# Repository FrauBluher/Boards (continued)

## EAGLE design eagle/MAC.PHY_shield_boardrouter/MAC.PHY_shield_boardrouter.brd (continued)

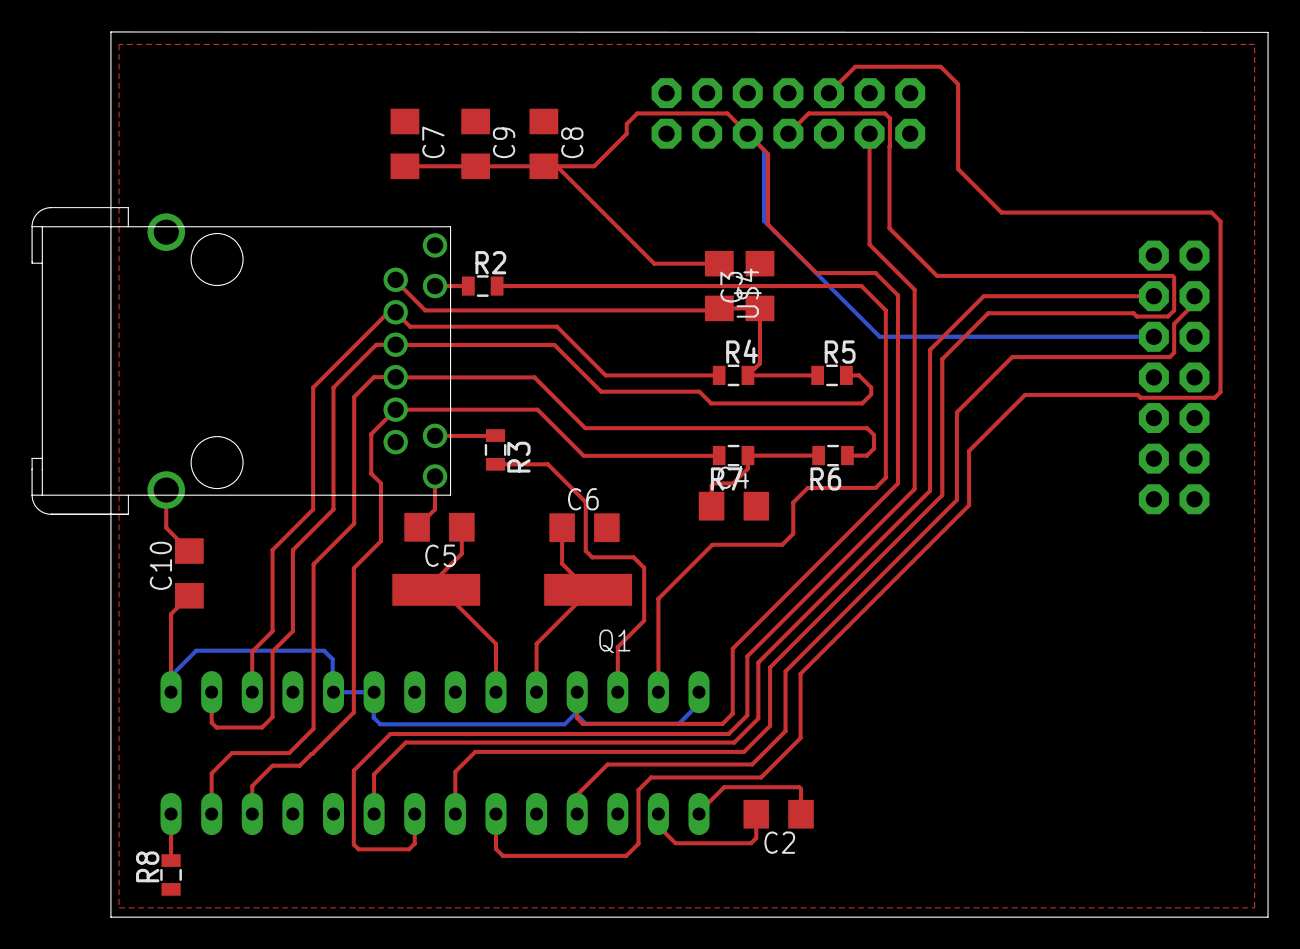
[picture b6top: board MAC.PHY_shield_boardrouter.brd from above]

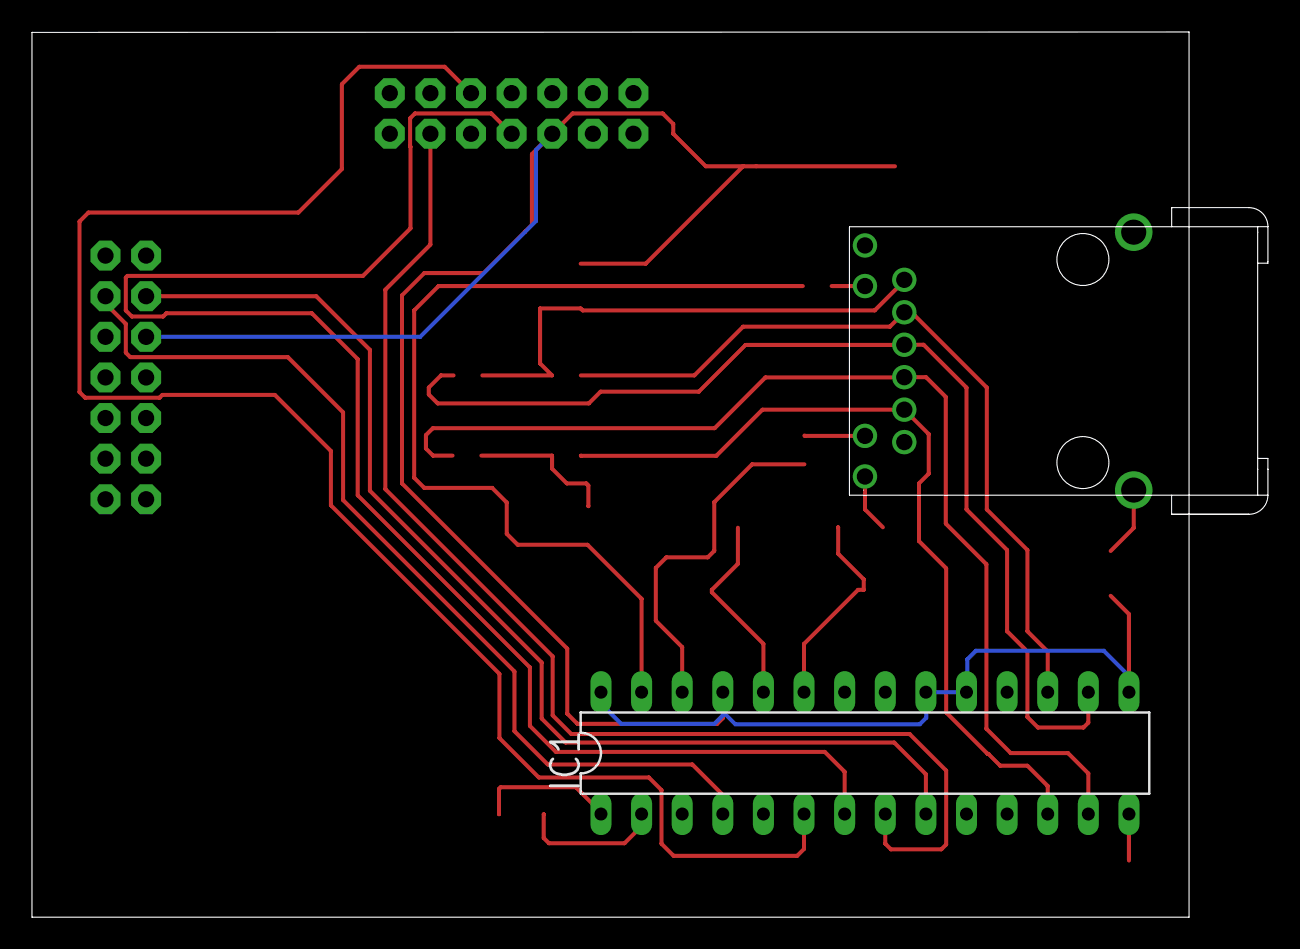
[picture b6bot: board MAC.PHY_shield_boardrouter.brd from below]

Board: 2 copper layers, 77.3 x 55.4 mm, 21 parts (2 on the bottom side), 21 nets.

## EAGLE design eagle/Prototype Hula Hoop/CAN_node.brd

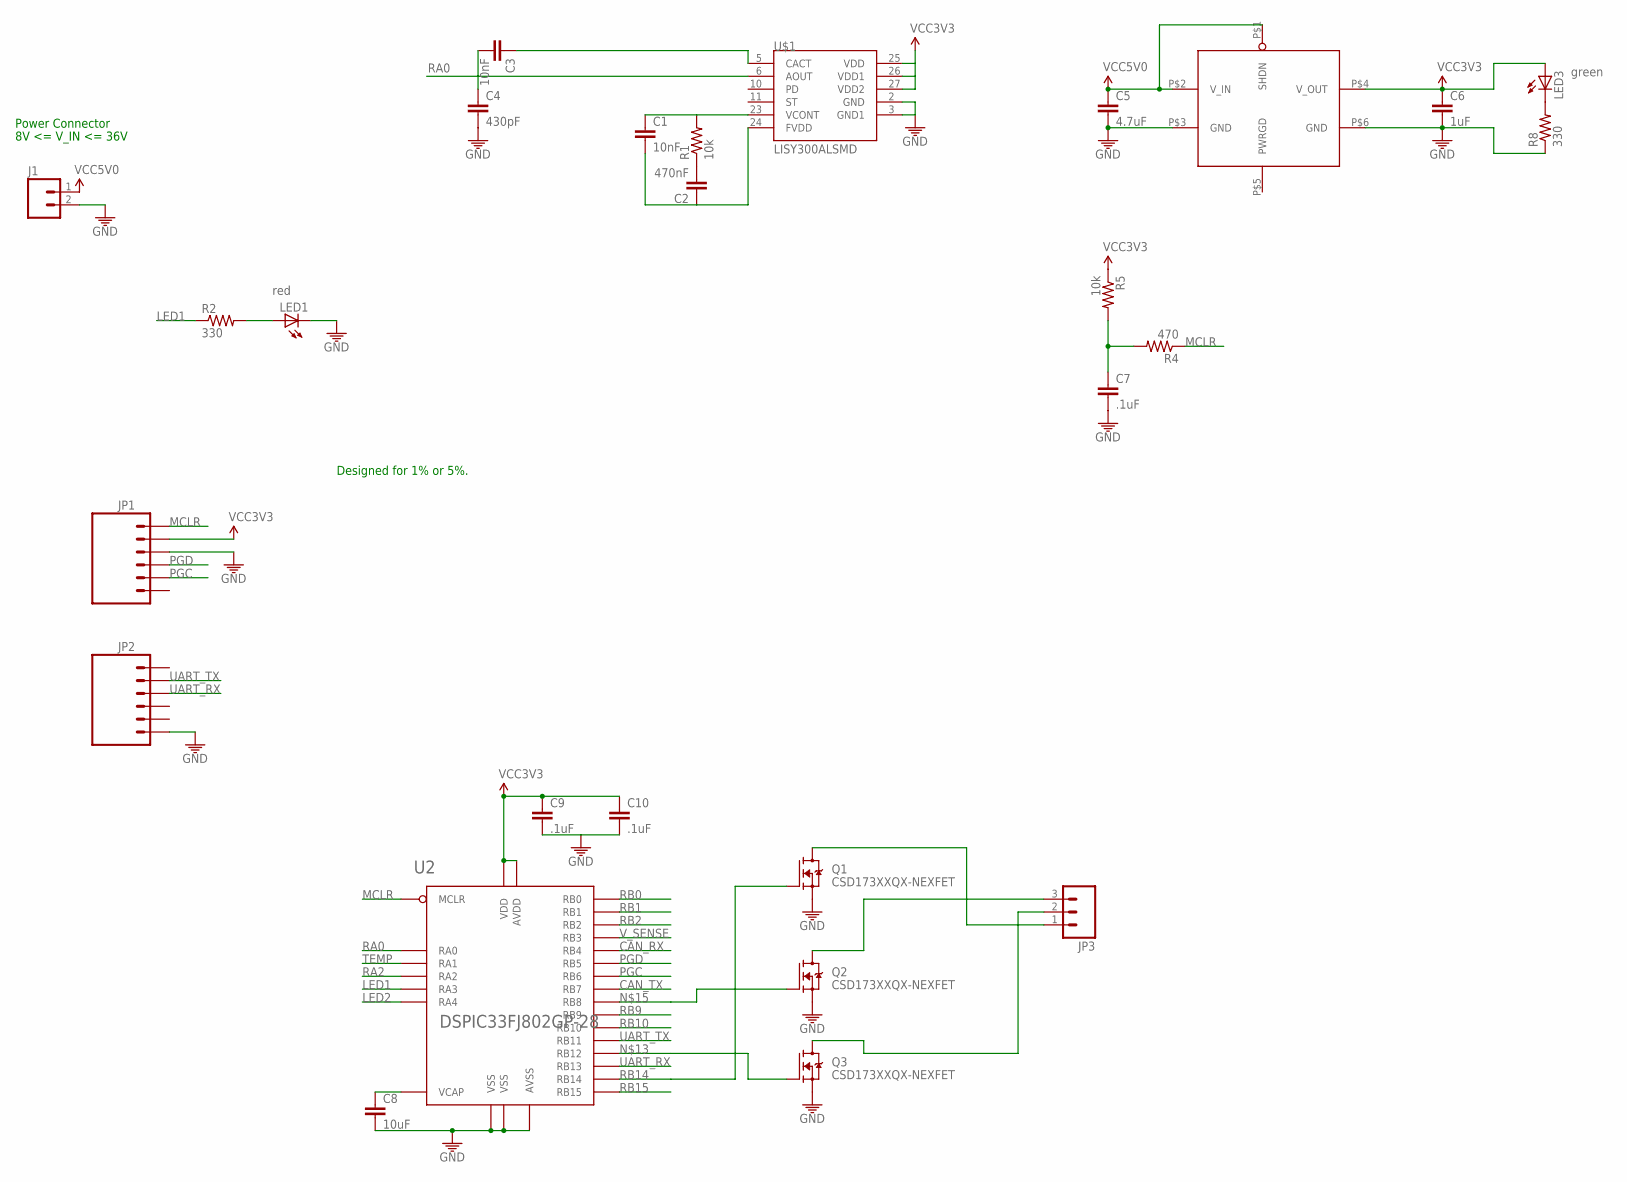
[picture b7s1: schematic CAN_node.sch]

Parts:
C1, C3: 10nF; 1206
C2: 470nF; 1206
C4: 430pF; 1206
C5: 4.7uF; 1206
C6: 1uF; 1206
C7, C9, C10: .1uF; 1206
C8: 10uF; 1206
J1: M02PTH; 1X02
JP1, JP2: M06LOCK; 1X06_LOCK
JP3: M03PTH; 1X03
LED1, LED3: LED1206; LED-1206
Q1, Q2, Q3: CSD173XXQX-NEXFET; CSD173XXQX
R1, R5: 10k; 0805
R2, R8: 330; 0805
R4: 470; 0805
U2: DSPIC33FJ802GP-28; SOIC28-W
U3: MCP1826; SOT223-5
U$1: LISY300ALSMD; LGA28

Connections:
CAN_RX: U2.P$11 (RB4)
CAN_TX: U2.P$16 (RB7)
GND: C4.2, C5.2, C6.2, C7.2, C8.2, C9.2, C10.2, J1.2 (1), JP1.3, JP2.6, LED1.C, Q1.S1 (S), Q1.S2 (S), Q1.S3 (S), Q2.S1 (S), Q2.S2 (S), Q2.S3 (S), Q3.S1 (S), Q3.S2 (S), Q3.S3 (S), R8.1, U2.P$8 (VSS), U2.P$19 (VSS), U2.P$27 (AVSS), U3.P$3 (GND), U3.P$6 (GND), U$1.2 (GND), U$1.3 (GND1)
LED1: R2.1, U2.P$10 (RA3)
LED2: U2.P$12 (RA4)
MCLR: JP1.1, R4.1, U2.P$1 (MCLR)
unnamed: LED1.A, R2.2
unnamed: C2.2, R1.1
unnamed: JP3.2, Q3.D
unnamed: JP3.1, Q1.D
unnamed: C1.1, R1.2, U$1.23 (VCONT)
unnamed: C7.1, R4.2, R5.2
unnamed: C8.1, U2.P$20 (VCAP)
unnamed: LED3.C, R8.2
unnamed: JP3.3, Q2.D
unnamed: C1.2, C2.1, U$1.24 (FVDD)
unnamed: C3.1, U$1.5 (CACT)
unnamed: Q3.G, U2.P$23 (RB12)
unnamed: Q2.G, U2.P$17 (RB8)
PGC: JP1.5, U2.P$15 (RB6)
PGD: JP1.4, U2.P$14 (RB5)
RA0: C3.2, C4.1, U2.P$2 (RA0), U$1.6 (AOUT)
RA2: U2.P$9 (RA2)
RB0: U2.P$4 (RB0)
RB1: U2.P$5 (RB1)
RB2: U2.P$6 (RB2)
RB9: U2.P$18 (RB9)
RB10: U2.P$22 (RB10)
RB14: Q1.G, U2.P$25 (RB14)
RB15: U2.P$26 (RB15)
TEMP: U2.P$3 (RA1)
UART_RX: JP2.3, U2.P$24 (RB13)
UART_TX: JP2.2, U2.P$21 (RB11)
VCC3V3: C6.1, C9.1, C10.1, JP1.2, LED3.A, R5.1, U2.P$13 (VDD), U2.P$28 (AVDD), U3.P$4 (V_OUT), U$1.25 (VDD), U$1.26 (VDD1), U$1.27 (VDD2)
VCC5V0: C5.1, J1.1 (2), U3.P$1 (SHDN), U3.P$2 (V_IN)
V_SENSE: U2.P$7 (RB3)

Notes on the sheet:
Power Connector
8V <= V_IN <= 36V
Designed for 1% or 5%.

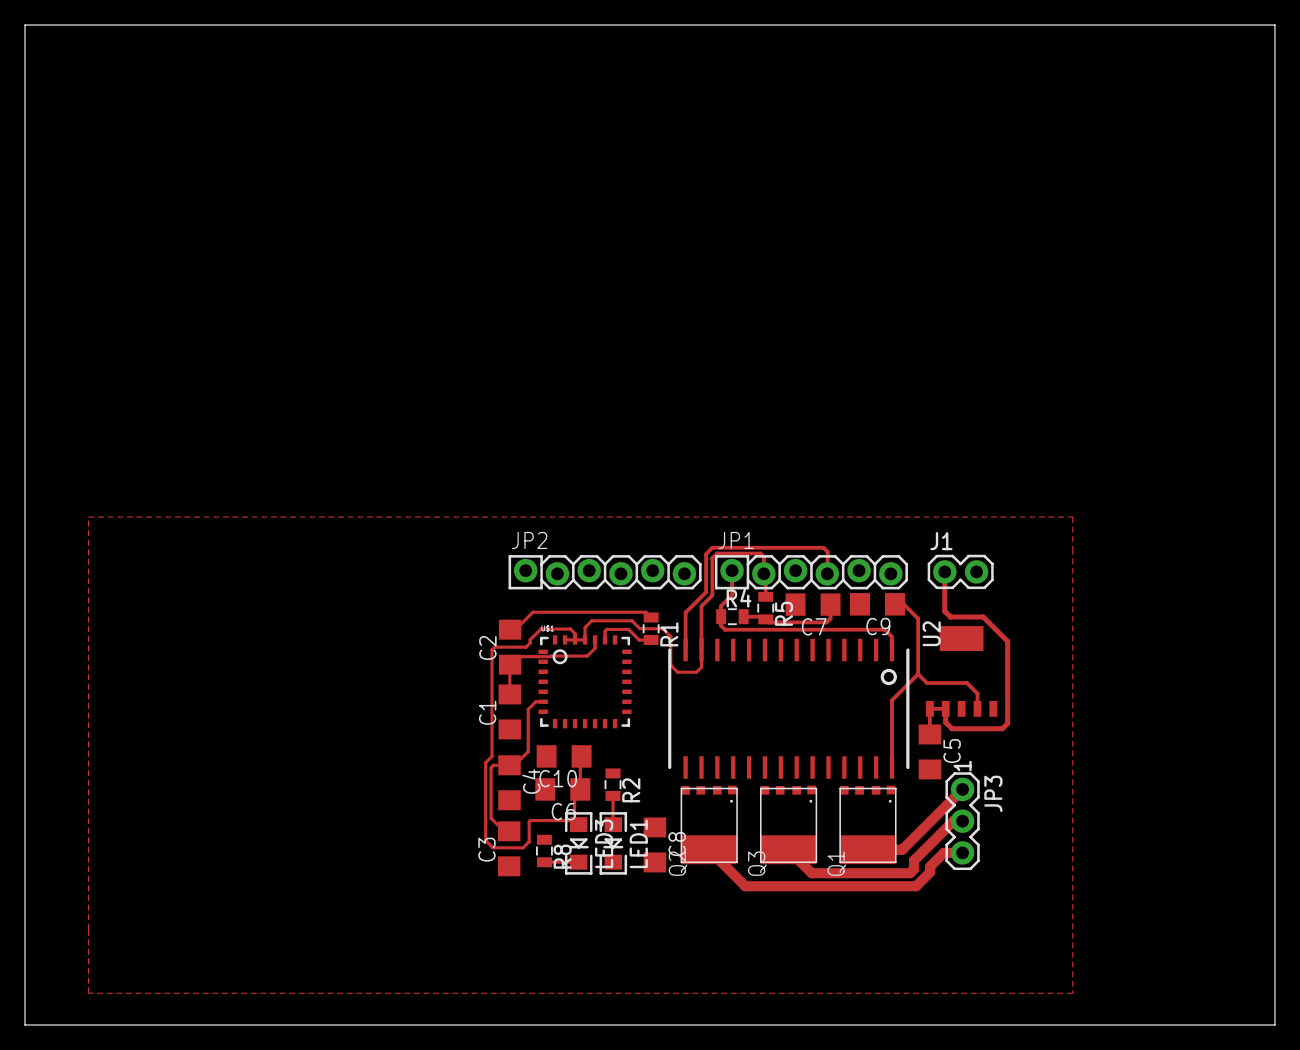
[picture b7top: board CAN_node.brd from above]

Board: 2 copper layers, 100.0 x 80.0 mm, 27 parts (0 on the bottom side), 24 nets.

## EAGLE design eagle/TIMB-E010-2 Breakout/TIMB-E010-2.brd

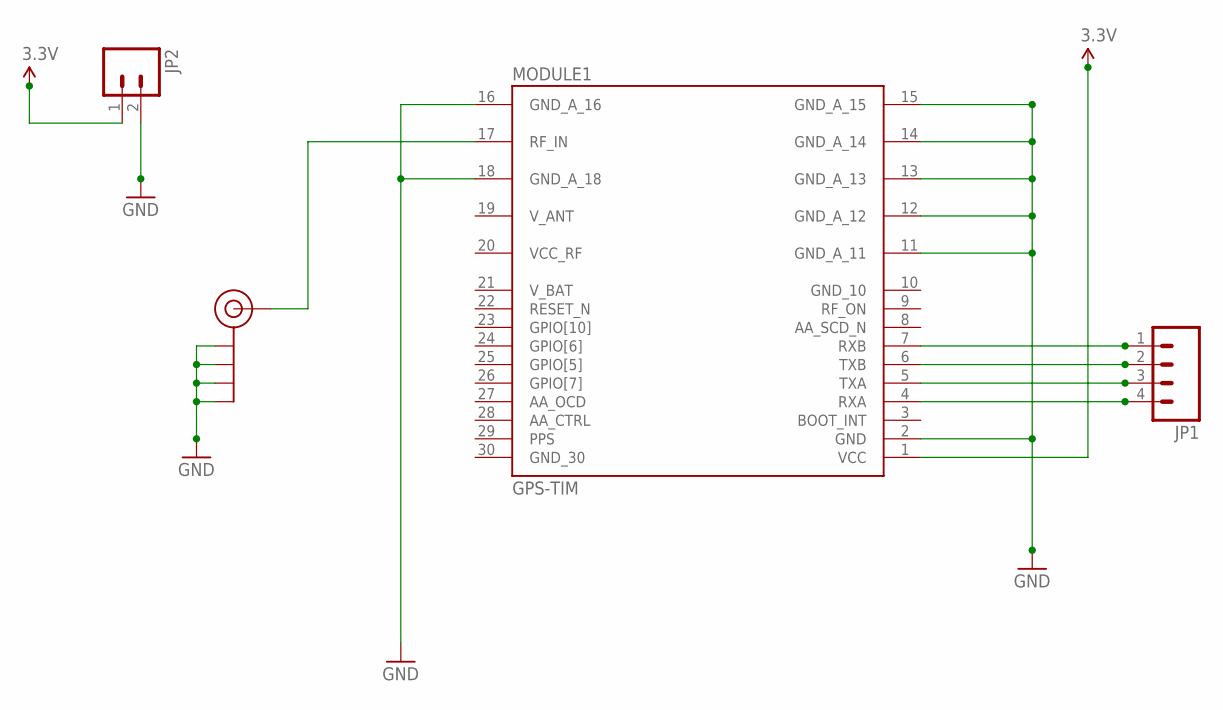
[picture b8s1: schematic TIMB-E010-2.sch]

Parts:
J$1: SMA_EDGE; SMA-EDGE
JP1: M04LOCK; 1X04_LOCK
JP2: M02LOCK; 1X02_LOCK
MODULE1: GPS-TIM; GPS_TIM

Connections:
3.3V: JP2.1, MODULE1.1 (VCC)
GND: J$1.GND@0 (GND), J$1.GND@1 (GND), J$1.GND@2 (GND), J$1.GND@3 (GND), JP2.2, MODULE1.2 (GND), MODULE1.11 (GND_A_11), MODULE1.12 (GND_A_12), MODULE1.13 (GND_A_13), MODULE1.14 (GND_A_14), MODULE1.15 (GND_A_15), MODULE1.16 (GND_A_16), MODULE1.18 (GND_A_18)
unnamed: J$1.SIG (SIGNAL), MODULE1.17 (RF_IN)
unnamed: JP1.3, MODULE1.5 (TXA)
unnamed: JP1.4, MODULE1.4 (RXA)
unnamed: JP1.1, MODULE1.7 (RXB)
unnamed: JP1.2, MODULE1.6 (TXB)

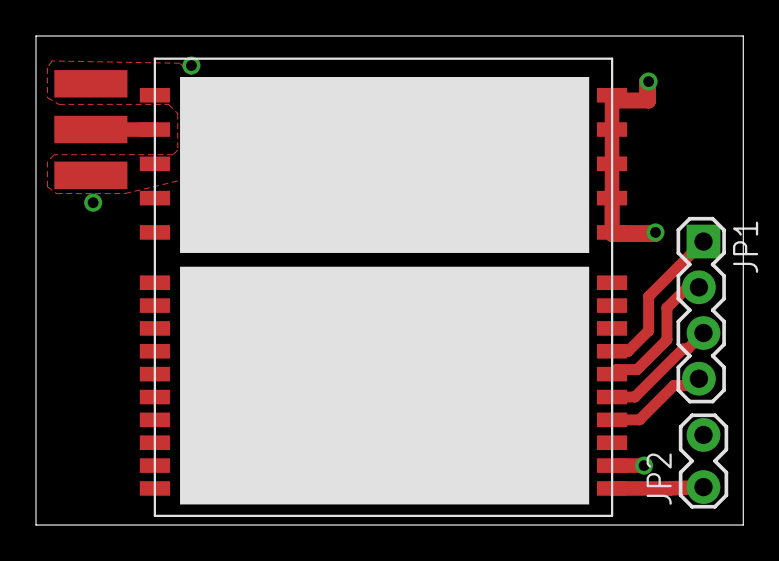
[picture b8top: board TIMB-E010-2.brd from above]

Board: 2 copper layers, 39.3 x 27.2 mm, 4 parts (0 on the bottom side), 7 nets.
